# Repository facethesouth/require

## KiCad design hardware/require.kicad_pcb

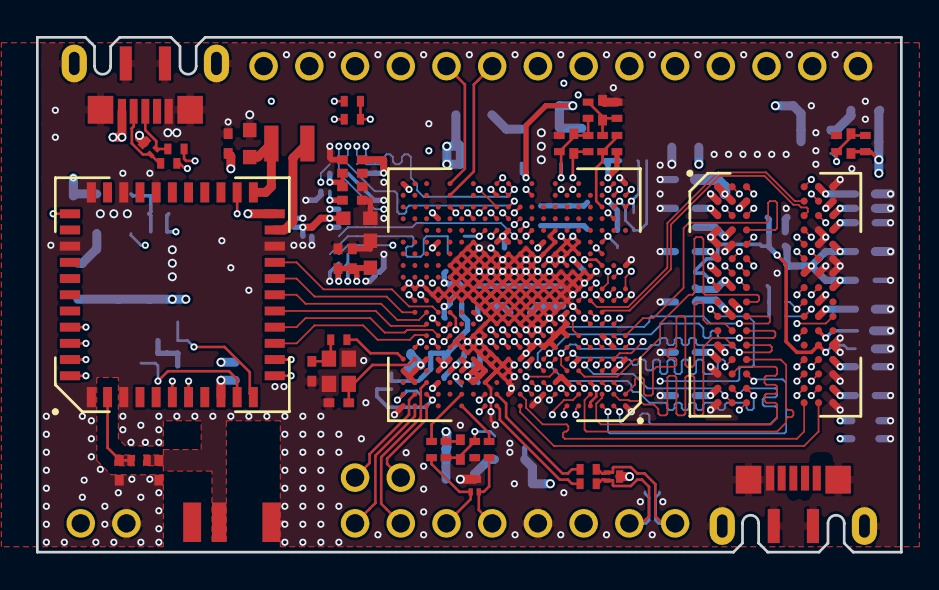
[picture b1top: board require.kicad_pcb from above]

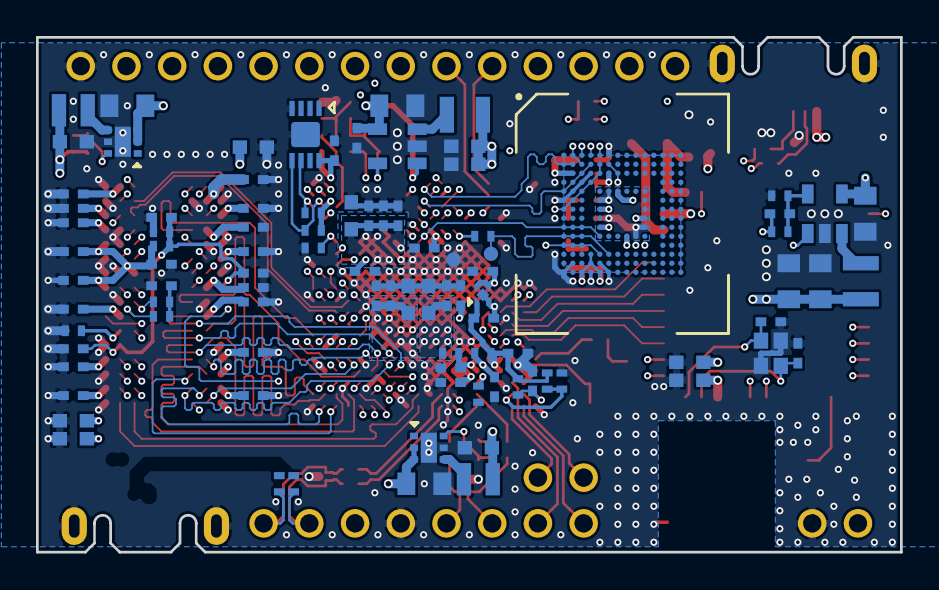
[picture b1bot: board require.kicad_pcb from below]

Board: 6 copper layers, 48.0 x 28.6 mm, 168 parts (93 on the bottom side), 145 nets.

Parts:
ANT1: ANT_LA52H2450_5500_A28; LA52H2450_5500_A28
C100, C101: 22p; C_0402
C110, C200, C206, C207, C226, C229, C255, C257, C265, C269, C310, C311, C312, C313, C314, C315, C316, C317, C318, C319, C320, C321, C322, C323, C324, C325, C326, C330, C351, C352, C401, C402, C406, C411: 0.1u; C_0402
C201, C221, C231, C251, C253, C254: 10u,10V; C_0805
C202, C222, C232, C252, C340: 100p; C_0402
C203, C204, C205: 22u; C_0603
C208, C405: 2.2u; C_0402
C210: 10n; C_0402
C223, C225, C233, C300, C301, C302, C350, C400, C410, C510, C511, C540: 10u; C_0603
C256, C258: 0.47u; C_0402
C260, C261, C420, C530, C830: 1u; C_0402
C331, C332: 1n; C_0402
C500, C501: C; C_0402
C520, C521: 15p; C_0402
D800, D810, D820: PESDUC3FD5VU; SOT-883
F229, F269: 180R,1.5A; L_0402
J800, J801: Molex 105164-0001; USB_Micro-B_Molex-105164-0001
L200, L250, L540: 2.2u; L_1008
L220, L230: 2.2u; L_0806
L500: L; L_0402
LP1: 3V3; OVAL_PIN
LP2, LP7: G; OVAL_PIN
LP3: A0; OVAL_PIN
LP4: A2; OVAL_PIN
LP5: D19; OVAL_PIN
LP6: D20; OVAL_PIN
LP8: 5V; OVAL_PIN
LP9: DM; OVAL_PIN
LP10: DP; OVAL_PIN
LP31: A1; OVAL_PIN
LP41: A3; OVAL_PIN
R50: 240R, 1%; R_0402
R100, R400, R800, R801, R810, R811, R812, R813, R820, R821: 22R; R_0402
R110, R840, R841: 10k; R_0402
R202, R233: 100k,1%; R_0402
R203, R223, R232, R252: 150k,1%; R_0402
R210: 169k,1%; R_0402
R211: 10k,1%; R_0402
R212: 27k,1%; R_0402
R213: 12k,1%; R_0402
R222: 110k,1%; R_0402
R253: 33k,1%; R_0402
R330, R331: 1k,1%; R_0402
R340, R341: 49.9R,1%; R_0402
R410: 2.2k; R_0402
R700, R701: 51k,1%; R_0402
R805: 133R,1%; R_0402
R830, R831: 4.7k; R_0402
RP1: 1; OVAL_PIN
RP2: 2; OVAL_PIN
RP3: 3; OVAL_PIN
RP4: 4; OVAL_PIN
RP5: 5; OVAL_PIN
RP6: 6; OVAL_PIN
RP7: 7; OVAL_PIN
RP8: 8; OVAL_PIN
RP9: 9; OVAL_PIN
RP10: 10; OVAL_PIN
RP11: 11; OVAL_PIN
RP12: 12; OVAL_PIN
RP13: 13; OVAL_PIN
RP14: G; OVAL_PIN
TP100, TP101: TestPoint; TP08
U100: RK3308; RK3308_TFBGA-355
U200, U250: SY8089AAC; SOT-23-5
U220, U230: PAM2305CGFADJ; U-DFN2020-6
U260: NCP707CMX180TCG; XDFN4
U300: DDR3_FBGA96; DDR3_BGA-96
U400: EMMC_BGA_153; BGA-153_14x14_11.5x13.0mm
U500: ap6255; AP6255_QFP_44
U830: ATECC608A-MAHDA; ATECC_UDFN8
Y100: 24MHz,12pF,10ppm; Crystal_SMD_2016-4pin_2.0x1.6mm
Y520: 37.4MHz,9pF,10ppm; Crystal_SMD_2016-4pin_2.0x1.6mm

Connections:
+1V0: C229.1, F229.2, U100.D15, U100.E15
+1V0C: C202.1, C203.1, C204.1, C205.1, C206.1, C207.1, C208.1, L200.2, R202.1, U100.N6, U100.N7, U100.N8, U100.P5, U100.P6, U100.P7, U100.R5, U100.R6, U100.R8
+1V0L: C222.1, C223.1, C225.1, C226.1, F229.1, L220.2, R222.1, U100.F10, U100.F11, U100.F12, U100.G10, U100.G11, U100.G12
+1V8: C261.1, C265.1, F269.1, R110.1, R700.1, U100.D17, U100.E16, U100.E17, U260.1
+1V8A: C269.1, F269.2, U100.D16
+3V3: C252.1, C253.1, C254.1, C255.1, C256.1, C257.1, C258.1, C260.1, C400.1, C401.1, C402.1, C405.1, C406.1, C410.1, C411.1, C510.1, C511.1, C530.1, C830.1, L250.2, LP1.1, R213.1, R252.1, R830.1, R831.1, R840.1, R841.1, U100.C14, U100.D13, U100.D14, U100.E14, U100.J14, U100.N5, U100.R11, U100.R12, U100.T11, U260.3, U260.4, U400.C6, U400.E6, U400.F5, U400.J10, U400.K9, U400.M4, U400.N4, U400.P3, U400.P5, U500.9, U500.22, U830.8
+5V: C200.1, C201.1, C221.1, C231.1, C251.1, J800.1, J801.1, LP8.1, U200.1, U200.4, U220.2, U220.3, U230.2, U230.3, U250.1, U250.4
/USB_HOST_D1_N: R810.2, U100.A12
/USB_HOST_D1_P: R811.2, U100.B12
/USB_HOST_D2_N: D810.2, LP9.1, R810.1, R813.2
/USB_HOST_D2_P: D810.1, LP10.1, R811.1, R812.2
/USB_HOST_D3_N: J801.3, R812.1
/USB_HOST_D3_P: J801.2, R813.1
/USB_OTG_D_N: R801.2, U100.A13
/USB_OTG_D_P: R800.2, U100.B13
/ddr/DDR_A0: U100.B4, U300.N3
/ddr/DDR_A1: U100.A5, U300.P7
/ddr/DDR_A2: U100.A3, U300.P3
/ddr/DDR_A3: U100.E6, U300.N2
/ddr/DDR_A4: U100.B7, U300.P8
/ddr/DDR_A5: U100.B3, U300.P2
/ddr/DDR_A6: U100.A6, U300.R8
/ddr/DDR_A7: U100.A2, U300.R2
/ddr/DDR_A8: U100.A10, U300.T8
/ddr/DDR_A9: U100.E7, U300.R3
/ddr/DDR_A10: U100.C9, U300.L7
/ddr/DDR_A11: U100.B5, U300.R7
/ddr/DDR_A12: U100.B6, U300.N7
/ddr/DDR_A13: U100.D7, U300.T3
/ddr/DDR_A14: U100.B10, U300.T7
/ddr/DDR_BA0: U100.B2, U300.M2
/ddr/DDR_BA1: U100.C8, U300.N8
/ddr/DDR_BA2: U100.D6, U300.M3
/ddr/DDR_CASN: U100.D8, U300.K3
/ddr/DDR_CKE0: U100.B9, U300.K9
/ddr/DDR_CLKN: R340.2, U100.C2, U300.K7
/ddr/DDR_CLKP: R341.2, U100.C3, U300.J7
/ddr/DDR_CS0N: U100.B1, U300.L2
/ddr/DDR_D0: U100.J4, U300.C2
/ddr/DDR_D1: U100.G5, U300.A2
/ddr/DDR_D2: U100.H4, U300.C3
/ddr/DDR_D3: U100.L1, U300.A7
/ddr/DDR_D4: U100.E2, U300.C8
/ddr/DDR_D5: U100.F1, U300.A3
/ddr/DDR_D6: U100.E3, U300.D7
/ddr/DDR_D7: U100.K2, U300.B8
/ddr/DDR_D8: U100.F4, U300.H7
/ddr/DDR_D9: U100.F3, U300.F2
/ddr/DDR_D10: U100.L4, U300.F7
/ddr/DDR_D11: U100.D3, U300.H8
/ddr/DDR_D12: U100.L2, U300.G2
/ddr/DDR_D13: U100.G2, U300.E3
/ddr/DDR_D14: U100.M2, U300.F8
/ddr/DDR_D15: U100.K5, U300.H3
/ddr/DDR_DM0: U100.G1, U300.D3
/ddr/DDR_DM1: U100.L3, U300.E7
/ddr/DDR_DQS0N: U100.K4, U300.B7
/ddr/DDR_DQS0P: U100.J3, U300.C7
/ddr/DDR_DQS1N: U100.H3, U300.G3
/ddr/DDR_DQS1P: U100.H2, U300.F3
/ddr/DDR_ODT0: U100.C5, U300.K1
/ddr/DDR_RASN: U100.D5, U300.J3
/ddr/DDR_RESET: U100.E4, U300.T2
/ddr/DDR_WEN: U100.E8, U300.L3
/emmc/EMMC_CLK: R400.2, U100.T13
/emmc/EMMC_CMD: U100.V13, U400.L1, U400.L2, U400.L3, U400.M5
/emmc/EMMC_D0: U100.U11, U400.A3
/emmc/EMMC_D1: U100.V12, U400.A4
/emmc/EMMC_D2: U100.Y12, U400.A5
/emmc/EMMC_D3: U100.Y11, U400.B1, U400.B2
/emmc/EMMC_D4: U100.W11, U400.A2, U400.B3
/emmc/EMMC_D5: U100.V11, U400.B4, U400.C3, U400.D2, U400.E1
/emmc/EMMC_D6: U100.U10, U400.B5, U400.C5, U400.D4, U400.E3, U400.F2, U400.G1
/emmc/EMMC_D7: U100.U12, U400.B6, U400.C7
/emmc/EMMC_RST: U100.R10, U400.J1, U400.J2, U400.J3, U400.K5
/emmc/VDDi: C420.1, U400.C1, U400.C2
/power/CORE_DVS: R212.2, R213.2, U100.V3
/rk3308-io/A0: LP3.1, U100.A19
/rk3308-io/A1: LP31.1, U100.B19
/rk3308-io/A2: LP4.1, U100.C18
/rk3308-io/A3: LP41.1, U100.A18
/rk3308-io/A4: R700.2, R701.1, U100.B18
/rk3308-io/BT_REG_ON: U100.F19, U500.34
/rk3308-io/BT_WAKE_HOST: U100.H16, U500.7
/rk3308-io/D1: R840.2, RP1.1, U100.W12
/rk3308-io/D2: R841.2, RP2.1, U100.T12
/rk3308-io/D3: RP3.1, U100.U14
/rk3308-io/D4: RP4.1, U100.V16
/rk3308-io/D5: RP5.1, U100.Y16
/rk3308-io/D6: RP6.1, U100.W16
/rk3308-io/D7: RP7.1, U100.W9
/rk3308-io/D8: RP8.1, U100.T9
/rk3308-io/D9: RP9.1, U100.V10
/rk3308-io/D10: RP10.1, U100.T10
/rk3308-io/D11: RP11.1, U100.W2
/rk3308-io/D12: RP12.1, U100.W1
/rk3308-io/D13: RP13.1, U100.U2
/rk3308-io/D19: R820.2, U100.B15
/rk3308-io/D20: R821.2, U100.A15
/rk3308-io/EMMC_VSEL: R410.1, U100.R3
/rk3308-io/HOST_WAKE_BT: U100.G16, U500.6
/rk3308-io/I2C1_SCL: R830.2, U100.V1, U830.6
/rk3308-io/I2C1_SDA: R831.2, U100.V2, U830.5
/rk3308-io/SDIO_CLK: U100.J18, U500.17
/rk3308-io/SDIO_CMD: U100.H18, U500.16
/rk3308-io/SDIO_D0: U100.J19, U500.18
/rk3308-io/SDIO_D1: U100.J17, U500.19
/rk3308-io/SDIO_D2: U100.G18, U500.14
/rk3308-io/SDIO_D3: U100.G17, U500.15
/rk3308-io/UART4_CTS: U100.K19, U500.41
/rk3308-io/UART4_RTS: U100.K18, U500.44
/rk3308-io/UART4_RXD: U100.F17, U500.42
/rk3308-io/UART4_TXD: U100.J16, U500.43
/rk3308-io/USB_EXTR: R805.1, U100.C15
/rk3308-io/WIFI_REG_ON: U100.P3, U500.12
/rk3308-io/WIFI_WAKE_HOST: U100.N3, U500.13
/wireless/LPO: U100.Y2, U500.24
/wireless/RFOUT: C501.1, L500.1, U500.2
GND: ANT1.2, ANT1.3, C100.2, C101.2, C110.2, C200.2, C201.2, C203.2, C204.2, C205.2, C206.2, C207.2, C208.2, C210.2, C221.2, C223.2, C225.2, C226.2, C229.2, C231.2, C233.2, C251.2, C253.2, C254.2, C255.2, C256.2, C257.2, C258.2, C260.2, C261.2, C265.2, C269.2, C300.2, C301.2, C302.2, C310.2, C311.2, C312.2, C313.2, C314.2, C315.2, C316.2, C317.2, C318.2, C319.2, C320.2, C321.2, C322.2, C323.2, C324.2, C325.2, C326.2, C330.2, C331.2, C332.2, C340.2, C350.2, C351.2, C352.2, C400.2, C401.2, C402.2, C405.2, C406.2, C410.2, C411.2, C420.2, C500.1, C500.2, C501.2, C510.2, C511.2, C520.2, C521.2, C530.2, C540.2, C830.2, D800.3, D810.3, D820.3, J800.5, J800.6, J801.5, J801.6, L500.2, LP2.1, LP7.1, R50.2, R203.2, R211.2, R223.2, R233.2, R253.2, R331.2, R410.2, R701.2, R805.2, RP14.1, TP101.1, U100.A1, U100.A4, U100.A9, U100.A20, U100.B8, U100.B11, U100.C4, U100.C6, U100.C7, U100.C11, U100.C13, U100.C17, U100.C19, U100.D2, U100.D11, U100.D12, U100.D19, U100.D20, U100.E1, U100.E5, U100.E9, U100.E11, U100.E12, U100.E13, U100.E18, U100.F2, U100.F13, U100.F14, U100.F15, U100.F16, U100.G3, U100.G8, U100.G9, U100.G13, U100.G14, U100.G15, U100.H7, U100.H8, U100.H9, U100.H10, U100.H11, U100.H12, U100.H13, U100.H17, U100.J5, U100.J7, U100.J8, U100.J9, U100.J10, U100.J11, U100.J12, U100.J13, U100.K1, U100.K3, U100.K7, U100.K8, U100.K9, U100.K10, U100.K11, U100.K12, U100.K13, U100.K14, U100.K15, U100.K16, U100.K17, U100.L5, U100.L7, U100.L8, U100.L9, U100.L10, U100.L11, U100.L12, U100.L13, U100.L14, U100.L15, U100.L16, U100.L17, U100.L18, U100.L19, U100.L20, U100.M4, U100.M5, U100.M6, U100.M7, U100.M8, U100.M9, U100.M10, U100.M11, U100.M12, U100.M13, U100.M14, U100.M15, U100.M16, U100.N1, U100.N9, U100.N10, U100.N11, U100.N12, U100.N13, U100.N14, U100.N15, U100.N16, U100.P8, U100.P9, U100.P10, U100.P11, U100.P12, U100.P13, U100.P14, U100.P15, U100.R7, U100.R14, U100.R17, U100.T7, U100.U17, U100.Y1, U100.Y20, U200.2, U220.5, U220.7, U230.5, U230.7, U250.2, U260.2, U260.5, U300.A9, U300.B1, U300.B3, U300.B9, U300.D1, U300.D8, U300.E1, U300.E2, U300.E8, U300.F9, U300.G1, U300.G8, U300.G9, U300.J2, U300.J8, U300.M1, U300.M9, U300.P1, U300.P9, U300.T1, U300.T9, U400.A6, U400.C4, U400.D3, U400.E2, U400.E7, U400.F1, U400.G5, U400.H10, U400.J5, U400.K8, U400.N2, U400.N5, U400.P1, U400.P4, U400.P6, U500.1, U500.3, U500.20, U500.29, U500.31, U500.33, U500.36, U830.4, U830.9, Y100.2, Y100.4, Y520.2, Y520.4
unnamed: C100.1, R100.1, Y100.1
unnamed: C101.1, U100.E19, Y100.3
unnamed: C110.1, R110.2, U100.B20
unnamed: C202.2, R202.2, R203.1, R210.1, U200.5
unnamed: C210.1, R210.2, R211.1, R212.1
unnamed: C222.2, R222.2, R223.1, U220.6
unnamed: C232.2, R232.2, R233.1, U230.6
unnamed: C252.2, R252.2, R253.1, U250.5
unnamed: C330.1, C331.1, C332.1, R330.2, R331.1, U300.H1, U300.M8
unnamed: C340.1, R340.1, R341.1
unnamed: C520.1, U500.10, Y520.1
unnamed: C521.1, U500.11, Y520.3
unnamed: C540.1, L540.2, U500.23
unnamed: D800.1, J800.2, R801.1
unnamed: D800.2, J800.3, R800.1
unnamed: D820.1, LP5.1, R820.1
unnamed: D820.2, LP6.1, R821.1
unnamed: L200.1, U200.3
unnamed: L220.1, U220.4
unnamed: L230.1, U230.4
unnamed: L250.1, U250.3
unnamed: L540.1, U500.21
unnamed: R50.1, U300.L8
unnamed: R100.2, U100.E20
unnamed: R400.1, TP100.1, U400.K1, U400.K2, U400.K3, U400.M6
VCC_DDR: C232.1, C233.1, C300.1, C301.1, C302.1, C310.1, C311.1, C312.1, C313.1, C314.1, C315.1, C316.1, C317.1, C318.1, C319.1, C320.1, C321.1, C322.1, C323.1, C324.1, C325.1, C326.1, C350.1, C351.1, C352.1, L230.2, R232.1, R330.1, U100.E10, U100.F7, U100.F8, U100.F9, U100.G6, U100.H6, U100.J6, U300.A1, U300.A8, U300.B2, U300.C1, U300.C9, U300.D2, U300.D9, U300.E9, U300.F1, U300.G7, U300.H2, U300.H9, U300.K2, U300.K8, U300.N1, U300.N9, U300.R1, U300.R9

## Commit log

2019-03-05 Set theme jekyll-theme-cayman
2019-05-15 prepare gerber and drill
2019-05-16 update ignore
2019-05-17 update bom, change 3.3V divider resistor value
2019-05-20 fix cpu grounding pin (bottom left)
2019-05-20 update doc
